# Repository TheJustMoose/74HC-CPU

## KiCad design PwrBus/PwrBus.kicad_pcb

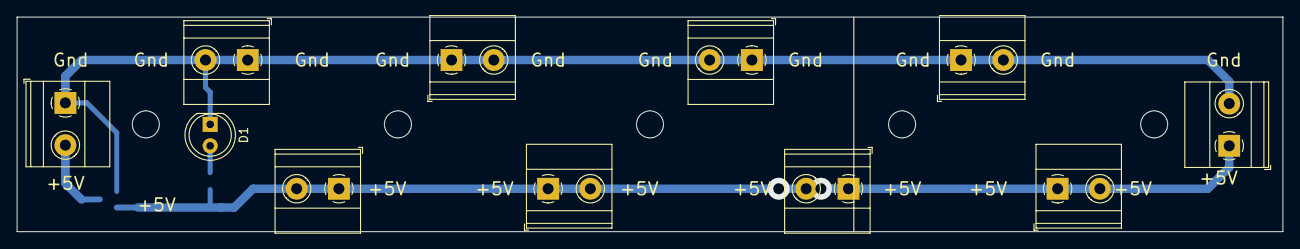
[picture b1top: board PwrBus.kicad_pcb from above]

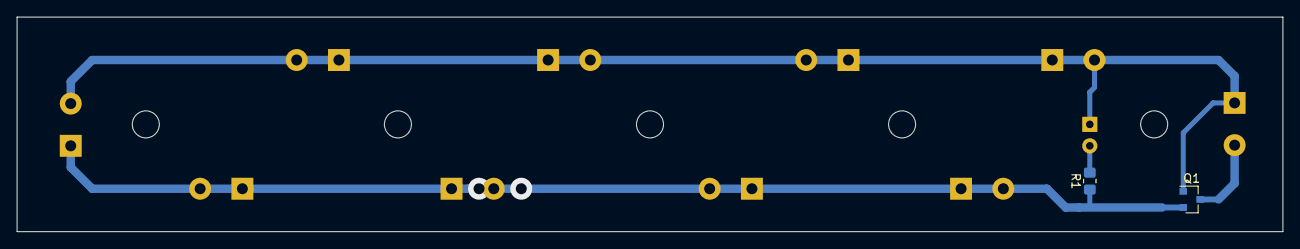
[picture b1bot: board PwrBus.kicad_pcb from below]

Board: 2 copper layers, 149.9 x 25.4 mm, 18 parts (2 on the bottom side), 4 nets.

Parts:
D1: LED; LED_D5.0mm
H1, H2, H3, H4, H5: MountingHole; MountingHole_3.2mm_M3
J1, J2, J3, J4, J5, J6, J7, J8, J9, J10: Screw_Terminal_01x02; TerminalBlock_Phoenix_MKDS-1,5-2_1x02_P5.00mm_Horizontal
Q1: IRLML5203; SOT-23
R1: 1k; R_0805_2012Metric_Pad1.20x1.40mm_HandSolder

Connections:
GND: D1.1, J1.1, J3.1, J3.2, J5.1, J5.2, J7.1, J7.2, J9.1, J9.2, J10.2, Q1.1
unnamed: D1.2, R1.2
unnamed: J1.2, Q1.3
VCC: J2.1, J2.2, J4.1, J4.2, J6.1, J6.2, J8.1, J8.2, J10.1, Q1.2, R1.1

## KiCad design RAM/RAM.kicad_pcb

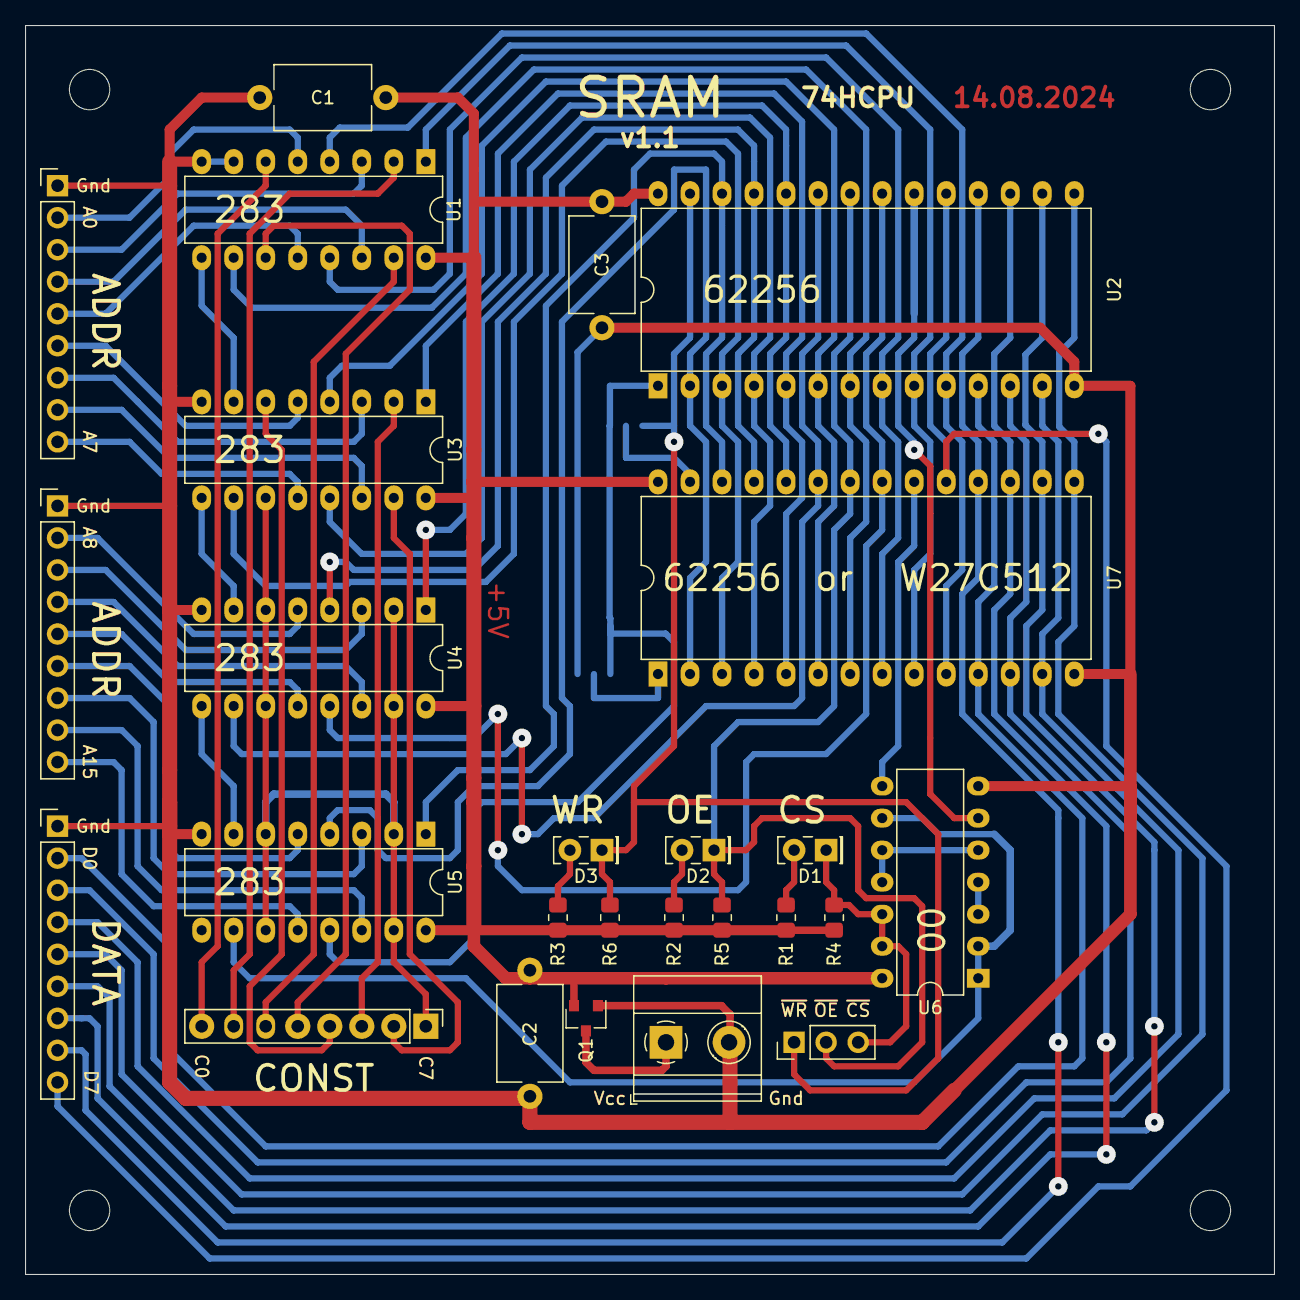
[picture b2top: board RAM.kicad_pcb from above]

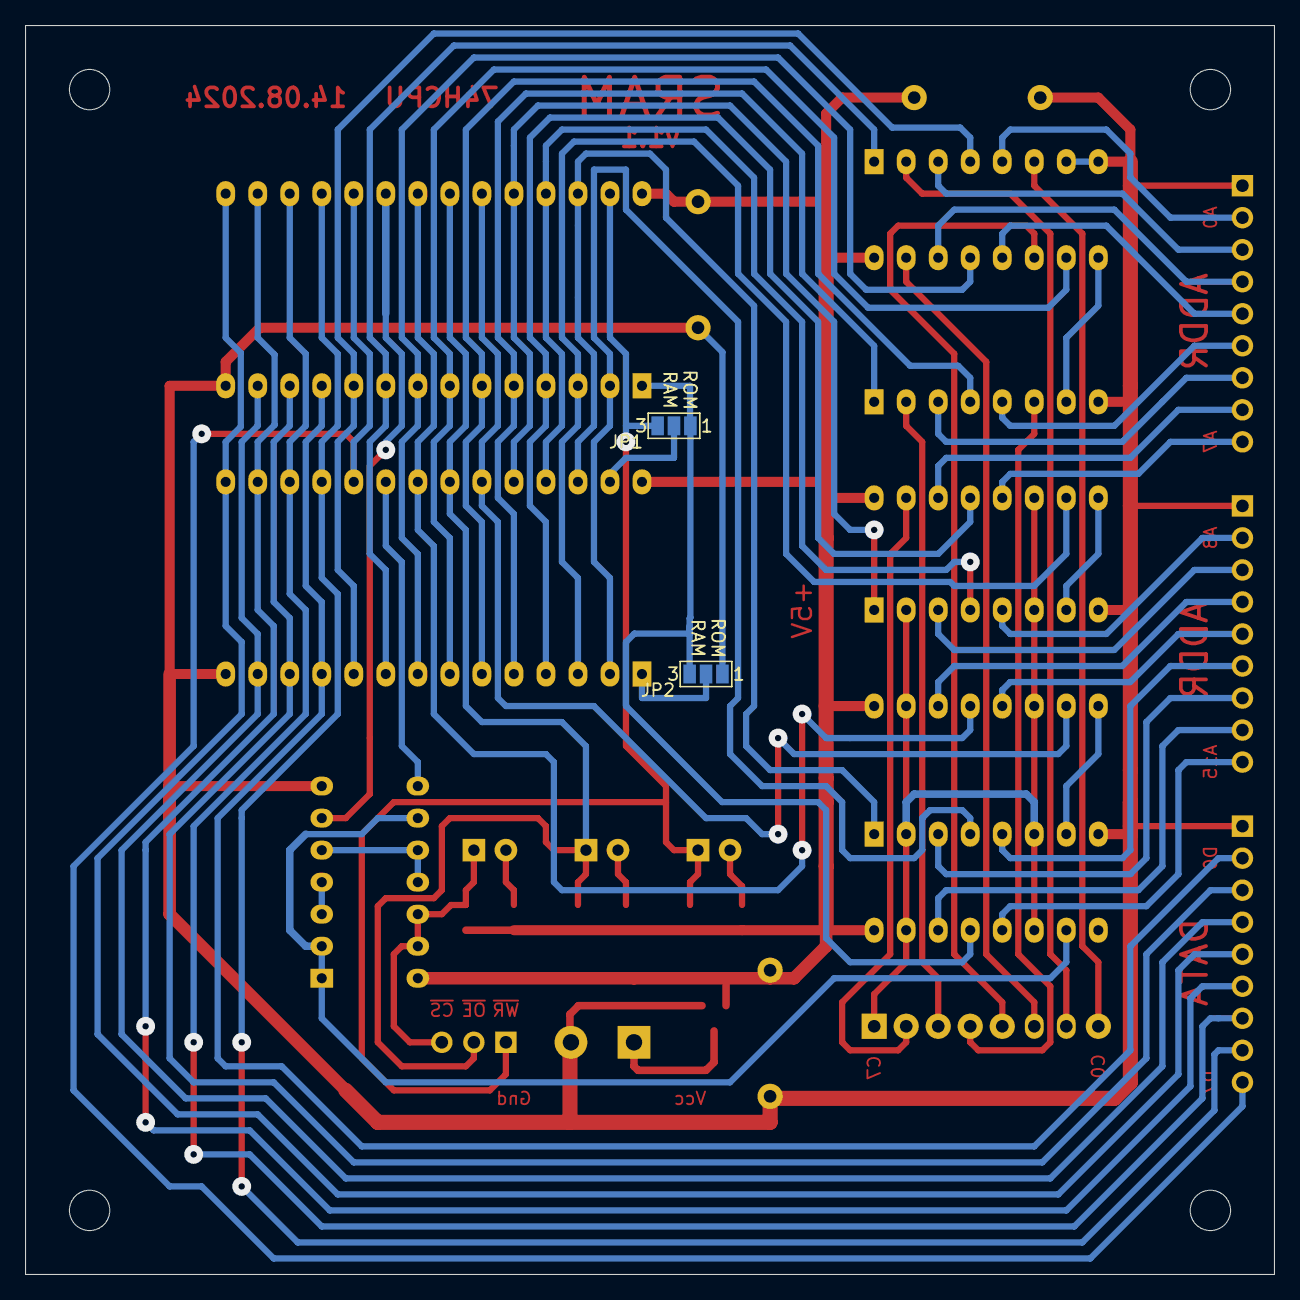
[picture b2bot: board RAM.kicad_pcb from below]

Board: 2 copper layers, 99.1 x 99.1 mm, 32 parts (2 on the bottom side), 66 nets.

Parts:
C1, C2, C3: 0.1uF; C_Disc_D7.5mm_W5.0mm_P10.00mm
D1, D2, D3: LED; LED_Rectangular_W5.0mm_H2.0mm
H1, H2, H3, H4: MountingHole; MountingHole_3.2mm_M3
J1, J2, J3: Conn_01x09_Male; PinHeader_1x09_P2.54mm_Vertical
J4: Conn_01x03_Male; PinHeader_1x03_P2.54mm_Vertical
J5: Conn_01x08_Male; PinHeader_1x08_P2.54mm_Vertical
J6: Screw_Terminal_01x02; TerminalBlock_Phoenix_MKDS-1,5-2_1x02_P5.00mm_Horizontal
JP1, JP2: SolderJumper_3_Bridged12; SolderJumper-3_P1.3mm_Open_Pad1.0x1.5mm_NumberLabels
Q1: IRLML5203; SOT-23
R1, R2, R3: 1k; R_0805_2012Metric_Pad1.20x1.40mm_HandSolder
R4, R5, R6: 10k; R_0805_2012Metric_Pad1.20x1.40mm_HandSolder
U1, U3, U4, U5: 74LS283; DIP-16_W7.62mm
U2: CY62256-70PC; DIP-28_W15.24mm
U6: 74HC00; DIP-14_W7.62mm
U7: W27C512; DIP-28_W15.24mm

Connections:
/A0: J1.2, U1.5
/A1: J1.3, U1.3
/A2: J1.4, U1.14
/A3: J1.5, U1.12
/A4: J1.6, U3.5
/A5: J1.7, U3.3
/A6: J1.8, U3.14
/A7: J1.9, U3.12
/A8: J2.2, U4.5
/A9: J2.3, U4.3
/A10: J2.4, U4.14
/A11: J2.5, U4.12
/A12: J2.6, U5.5
/A13: J2.7, U5.3
/A14: J2.8, U5.14
/A15: J2.9, U5.12
/AD0: U1.4, U2.10, U7.10
/AD1: U1.1, U2.9, U7.9
/AD2: U1.13, U2.8, U7.8
/AD3: U1.10, U2.7, U7.7
/AD4: U2.6, U3.4, U7.6
/AD5: U2.5, U3.1, U7.5
/AD6: U2.4, U3.13, U7.4
/AD7: U2.3, U3.10, U7.3
/AD8: U2.25, U4.4, U7.25
/AD9: U2.24, U4.1, U7.24
/AD10: U2.21, U4.13, U7.21
/AD11: U2.23, U4.10, U7.23
/AD12: U2.2, U5.4, U7.2
/AD13: U2.26, U5.1, U7.26
/AD14: JP1.1, JP2.3, U2.1, U5.13
/C0: J5.8, U1.6
/C1: J5.7, U1.2
/C2: J5.6, U1.15
/C3: J5.5, U1.11
/C4: J5.4, U3.6
/C5: J5.3, U3.2
/C6: J5.2, U3.15
/C7: J5.1, U3.11, U4.2, U4.6, U4.11, U4.15, U5.2, U5.6, U5.11, U5.15
/D0: J3.2, U2.11, U7.11
/D1: J3.3, U2.12, U7.12
/D2: J3.4, U2.13, U7.13
/D3: J3.5, U2.15, U7.15
/D4: J3.6, U2.16, U7.16
/D5: J3.7, U2.17, U7.17
/D6: J3.8, U2.18, U7.18
/D7: J3.9, U2.19, U7.19
/~CS: D1.1, J4.3, R4.2, U6.12, U6.13
/~CS1: U2.20, U6.6
/~CS2: U6.8, U7.20
/~OE: D2.1, J4.2, R5.2, U2.22, U7.22
/~WR: D3.1, J4.1, JP1.3, R6.2, U2.27
GND: C1.2, C2.2, C3.2, J1.1, J2.1, J3.1, J6.2, JP2.1, Q1.1, U1.7, U1.8, U2.14, U3.8, U4.8, U5.8, U6.7, U7.14
unnamed: D1.2, R1.2
unnamed: D2.2, R2.2
unnamed: D3.2, R3.2
unnamed: J6.1, Q1.3
unnamed: JP1.2, U7.27
unnamed: JP2.2, U7.1
unnamed: U1.9, U3.7
unnamed: U3.9, U4.7
unnamed: U4.9, U5.7
unnamed: U5.10, U6.1, U6.2, U6.9
unnamed: U6.3, U6.4
unnamed: U6.5, U6.10, U6.11
VCC: C1.1, C2.1, C3.1, Q1.2, R1.1, R2.1, R3.1, R4.1, R5.1, R6.1, U1.16, U2.28, U3.16, U4.16, U5.16, U6.14, U7.28

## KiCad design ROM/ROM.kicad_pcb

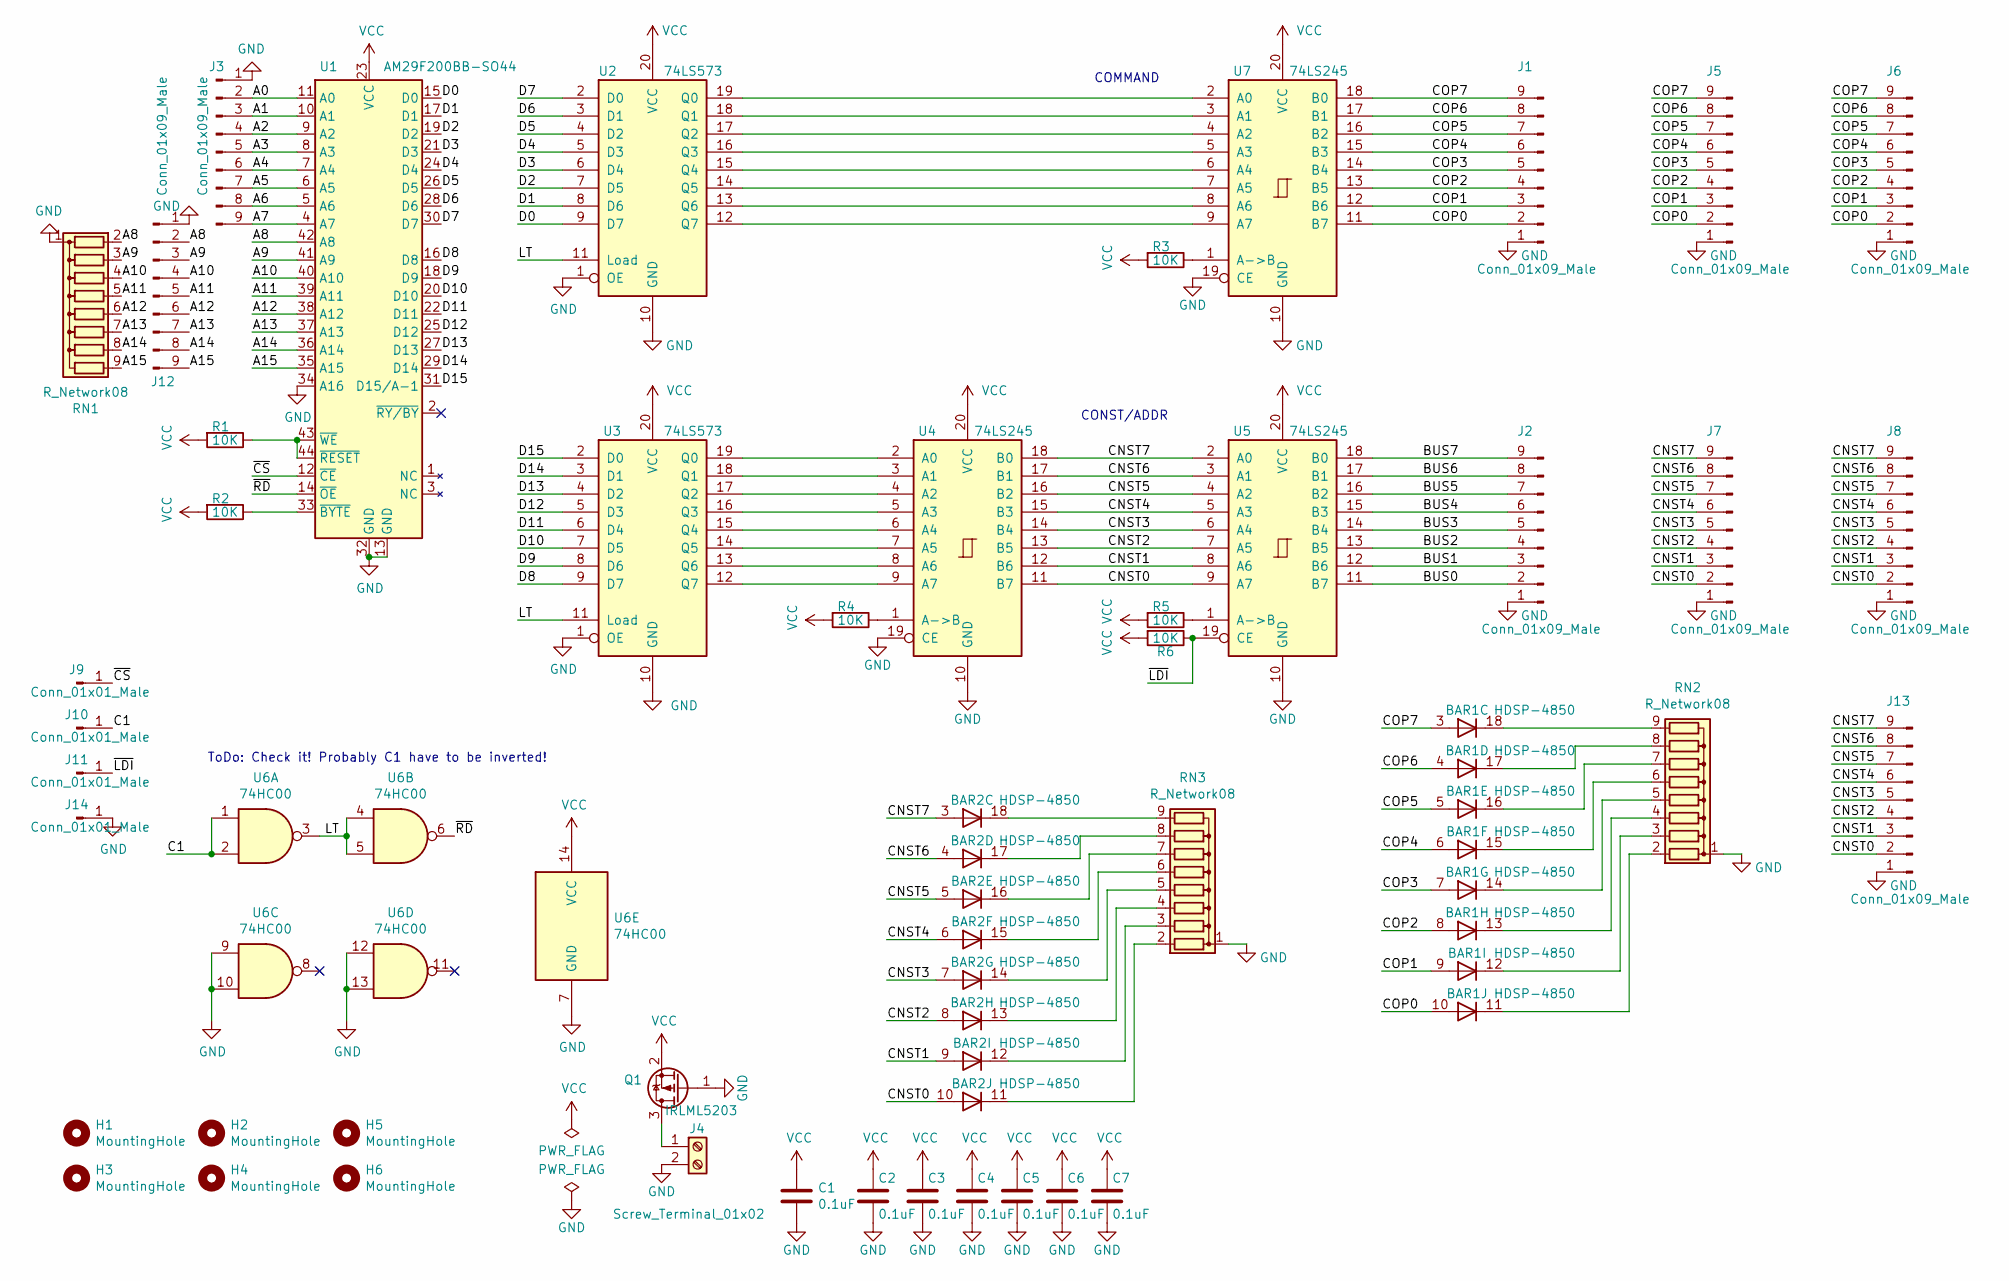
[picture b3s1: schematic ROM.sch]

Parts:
BAR1, BAR2: HDSP-4850
C1: 0.1uF; C_Rect_L24.0mm_W7.0mm_P22.50mm_MKT
C2, C3, C4, C5, C6, C7: 0.1uF; C_0805_2012Metric_Pad1.18x1.45mm_HandSolder
H1, H2, H3, H4, H5, H6: MountingHole; MountingHole_3.2mm_M3
J1, J2, J3, J5, J6, J7, J8, J12, J13: Conn_01x09_Male; PinHeader_1x09_P2.54mm_Vertical
J4: Screw_Terminal_01x02; TerminalBlock_Phoenix_PT-1,5-2-5.0-H_1x02_P5.00mm_Horizontal
J9, J10, J11, J14: Conn_01x01_Male; PinHeader_1x01_P2.54mm_Vertical
Q1: IRLML5203; SOT-23
R1, R2, R3, R4, R5, R6: 10K; R_0805_2012Metric_Pad1.20x1.40mm_HandSolder
RN1, RN2, RN3: R_Network08; R_Array_SIP9
U1: AM29F200BB-SO44; DIP-44_W15.24mm
U2, U3: 74LS573; DIP-20_W7.62mm
U4, U5, U7: 74LS245; DIP-20_W7.62mm
U6: 74HC00; DIP-14_W7.62mm

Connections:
/A0: J3.2, U1.11 (A0)
/A1: J3.3, U1.10 (A1)
/A2: J3.4, U1.9 (A2)
/A3: J3.5, U1.8 (A3)
/A4: J3.6, U1.7 (A4)
/A5: J3.7, U1.6 (A5)
/A6: J3.8, U1.5 (A6)
/A7: J3.9, U1.4 (A7)
/A8: J12.2, RN1.2 (R1), U1.42 (A8)
/A9: J12.3, RN1.3 (R2), U1.41 (A9)
/A10: J12.4, RN1.4 (R3), U1.40 (A10)
/A11: J12.5, RN1.5 (R4), U1.39 (A11)
/A12: J12.6, RN1.6 (R5), U1.38 (A12)
/A13: J12.7, RN1.7 (R6), U1.37 (A13)
/A14: J12.8, RN1.8 (R7), U1.36 (A14)
/A15: J12.9, RN1.9 (R8), U1.35 (A15)
/BUS0: J2.2, U5.11 (B7)
/BUS1: J2.3, U5.12 (B6)
/BUS2: J2.4, U5.13 (B5)
/BUS3: J2.5, U5.14 (B4)
/BUS4: J2.6, U5.15 (B3)
/BUS5: J2.7, U5.16 (B2)
/BUS6: J2.8, U5.17 (B1)
/BUS7: J2.9, U5.18 (B0)
/C1: J10.1, U6.1, U6.2
/CNST0: BAR2.10 (A), J7.2, J8.2, J13.2, U4.11 (B7), U5.9 (A7)
/CNST1: BAR2.9 (A), J7.3, J8.3, J13.3, U4.12 (B6), U5.8 (A6)
/CNST2: BAR2.8 (A), J7.4, J8.4, J13.4, U4.13 (B5), U5.7 (A5)
/CNST3: BAR2.7 (A), J7.5, J8.5, J13.5, U4.14 (B4), U5.6 (A4)
/CNST4: BAR2.6 (A), J7.6, J8.6, J13.6, U4.15 (B3), U5.5 (A3)
/CNST5: BAR2.5 (A), J7.7, J8.7, J13.7, U4.16 (B2), U5.4 (A2)
/CNST6: BAR2.4 (A), J7.8, J8.8, J13.8, U4.17 (B1), U5.3 (A1)
/CNST7: BAR2.3 (A), J7.9, J8.9, J13.9, U4.18 (B0), U5.2 (A0)
/COP0: BAR1.10 (A), J1.2, J5.2, J6.2, U7.11 (B7)
/COP1: BAR1.9 (A), J1.3, J5.3, J6.3, U7.12 (B6)
/COP2: BAR1.8 (A), J1.4, J5.4, J6.4, U7.13 (B5)
/COP3: BAR1.7 (A), J1.5, J5.5, J6.5, U7.14 (B4)
/COP4: BAR1.6 (A), J1.6, J5.6, J6.6, U7.15 (B3)
/COP5: BAR1.5 (A), J1.7, J5.7, J6.7, U7.16 (B2)
/COP6: BAR1.4 (A), J1.8, J5.8, J6.8, U7.17 (B1)
/COP7: BAR1.3 (A), J1.9, J5.9, J6.9, U7.18 (B0)
/D0: U1.15 (D0), U2.9 (D7)
/D1: U1.17 (D1), U2.8 (D6)
/D2: U1.19 (D2), U2.7 (D5)
/D3: U1.21 (D3), U2.6 (D4)
/D4: U1.24 (D4), U2.5 (D3)
/D5: U1.26 (D5), U2.4 (D2)
/D6: U1.28 (D6), U2.3 (D1)
/D7: U1.30 (D7), U2.2 (D0)
/D8: U1.16 (D8), U3.9 (D7)
/D9: U1.18 (D9), U3.8 (D6)
/D10: U1.20 (D10), U3.7 (D5)
/D11: U1.22 (D11), U3.6 (D4)
/D12: U1.25 (D12), U3.5 (D3)
/D13: U1.27 (D13), U3.4 (D2)
/D14: U1.29 (D14), U3.3 (D1)
/D15: U1.31 (D15/A-1), U3.2 (D0)
/LT: U2.11 (Load), U3.11 (Load), U6.3, U6.4, U6.5
/~CS: J9.1, U1.12 (~CE)
/~LDI: J11.1, R6.1, U5.19 (CE)
/~RD: U1.14 (~OE), U6.6
GND: C1.2, C2.2, C3.2, C4.2, C5.2, C6.2, C7.2, J1.1, J2.1, J3.1, J4.2, J5.1, J6.1, J7.1, J8.1, J12.1, J13.1, J14.1, Q1.1 (G), RN1.1 (common), RN2.1 (common), RN3.1 (common), U1.13 (GND), U1.32 (GND), U1.34 (A16), U2.1 (OE), U2.10 (GND), U3.1 (OE), U3.10 (GND), U4.10 (GND), U4.19 (CE), U5.10 (GND), U6.7 (GND), U6.9, U6.10, U6.12, U6.13, U7.10 (GND), U7.19 (CE)
unnamed: BAR1.11 (K), RN2.2 (R1)
unnamed: BAR1.12 (K), RN2.3 (R2)
unnamed: BAR1.13 (K), RN2.4 (R3)
unnamed: BAR1.14 (K), RN2.5 (R4)
unnamed: BAR1.15 (K), RN2.6 (R5)
unnamed: BAR1.16 (K), RN2.7 (R6)
unnamed: BAR1.17 (K), RN2.8 (R7)
unnamed: BAR1.18 (K), RN2.9 (R8)
unnamed: BAR2.11 (K), RN3.2 (R1)
unnamed: BAR2.12 (K), RN3.3 (R2)
unnamed: BAR2.13 (K), RN3.4 (R3)
unnamed: BAR2.14 (K), RN3.5 (R4)
unnamed: BAR2.15 (K), RN3.6 (R5)
unnamed: BAR2.16 (K), RN3.7 (R6)
unnamed: BAR2.17 (K), RN3.8 (R7)
unnamed: BAR2.18 (K), RN3.9 (R8)
unnamed: J4.1, Q1.3 (D)
unnamed: R1.1, U1.43 (~WE), U1.44 (~RESET)
unnamed: R2.1, U1.33 (~BYTE)
unnamed: R3.1, U7.1 (A->B)
unnamed: R4.1, U4.1 (A->B)
unnamed: R5.1, U5.1 (A->B)
unnamed: U2.12 (Q7), U7.9 (A7)
unnamed: U2.13 (Q6), U7.8 (A6)
unnamed: U2.14 (Q5), U7.7 (A5)
unnamed: U2.15 (Q4), U7.6 (A4)
unnamed: U2.16 (Q3), U7.5 (A3)
unnamed: U2.17 (Q2), U7.4 (A2)
unnamed: U2.18 (Q1), U7.3 (A1)
unnamed: U2.19 (Q0), U7.2 (A0)
unnamed: U3.12 (Q7), U4.9 (A7)
unnamed: U3.13 (Q6), U4.8 (A6)
unnamed: U3.14 (Q5), U4.7 (A5)
unnamed: U3.15 (Q4), U4.6 (A4)
unnamed: U3.16 (Q3), U4.5 (A3)
unnamed: U3.17 (Q2), U4.4 (A2)
unnamed: U3.18 (Q1), U4.3 (A1)
unnamed: U3.19 (Q0), U4.2 (A0)
VCC: C1.1, C2.1, C3.1, C4.1, C5.1, C6.1, C7.1, Q1.2 (S), R1.2, R2.2, R3.2, R4.2, R5.2, R6.2, U1.23 (VCC), U2.20 (VCC), U3.20 (VCC), U4.20 (VCC), U5.20 (VCC), U6.14 (VCC), U7.20 (VCC)

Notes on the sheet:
COMMAND
CONST/ADDR
ToDo: Check it! Probably C1 have to be inverted!

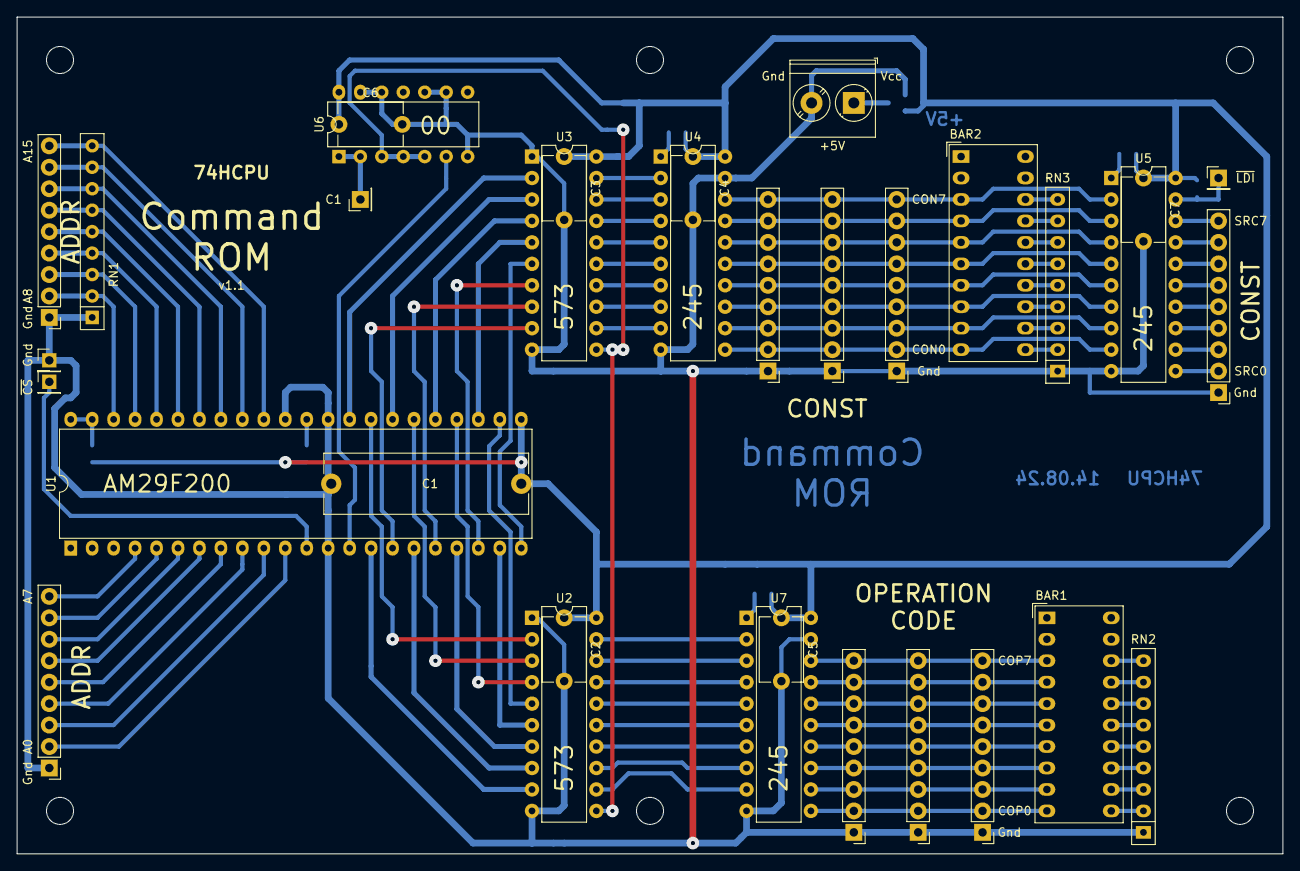
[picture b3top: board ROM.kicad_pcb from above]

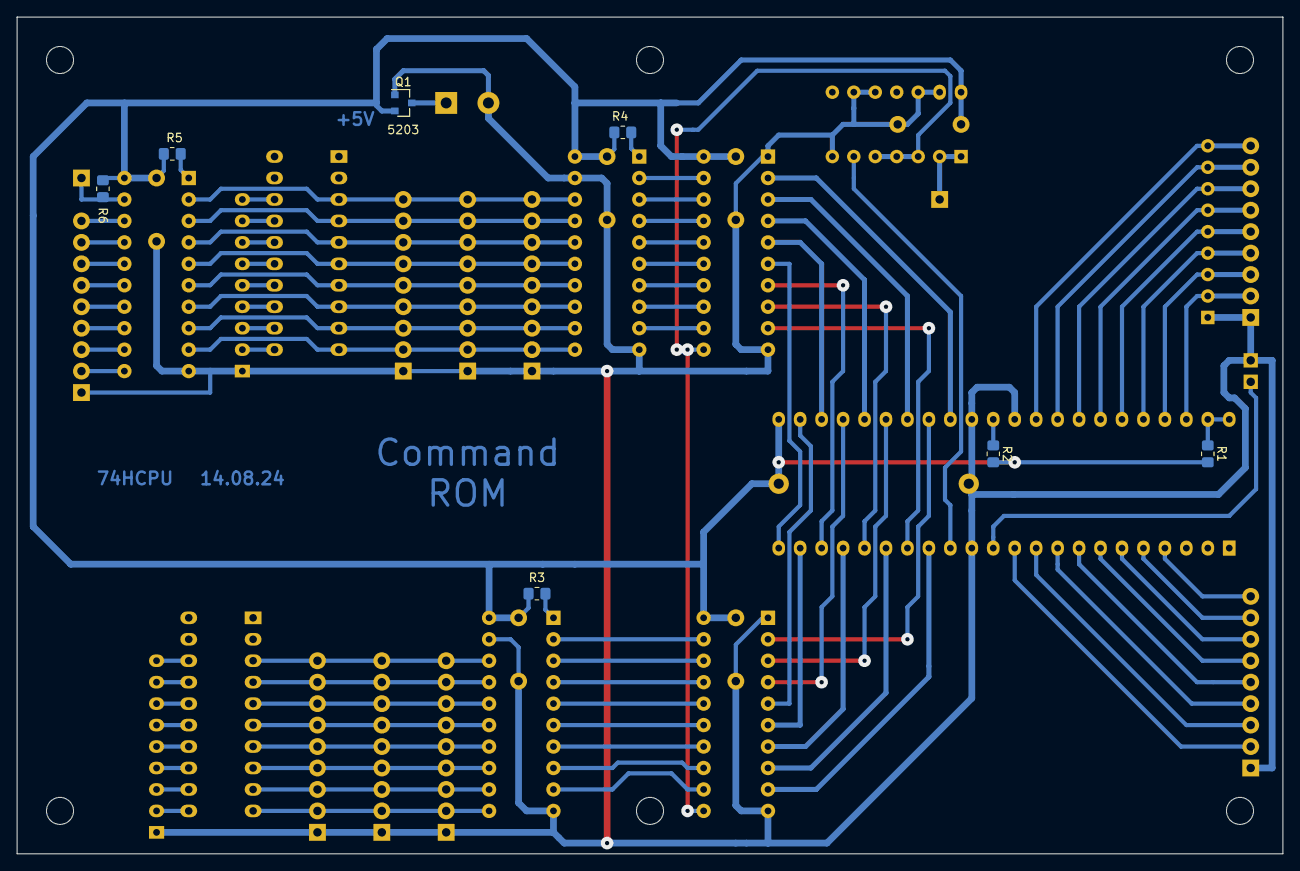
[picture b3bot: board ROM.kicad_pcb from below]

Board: 2 copper layers, 149.9 x 99.1 mm, 46 parts (7 on the bottom side), 101 nets.

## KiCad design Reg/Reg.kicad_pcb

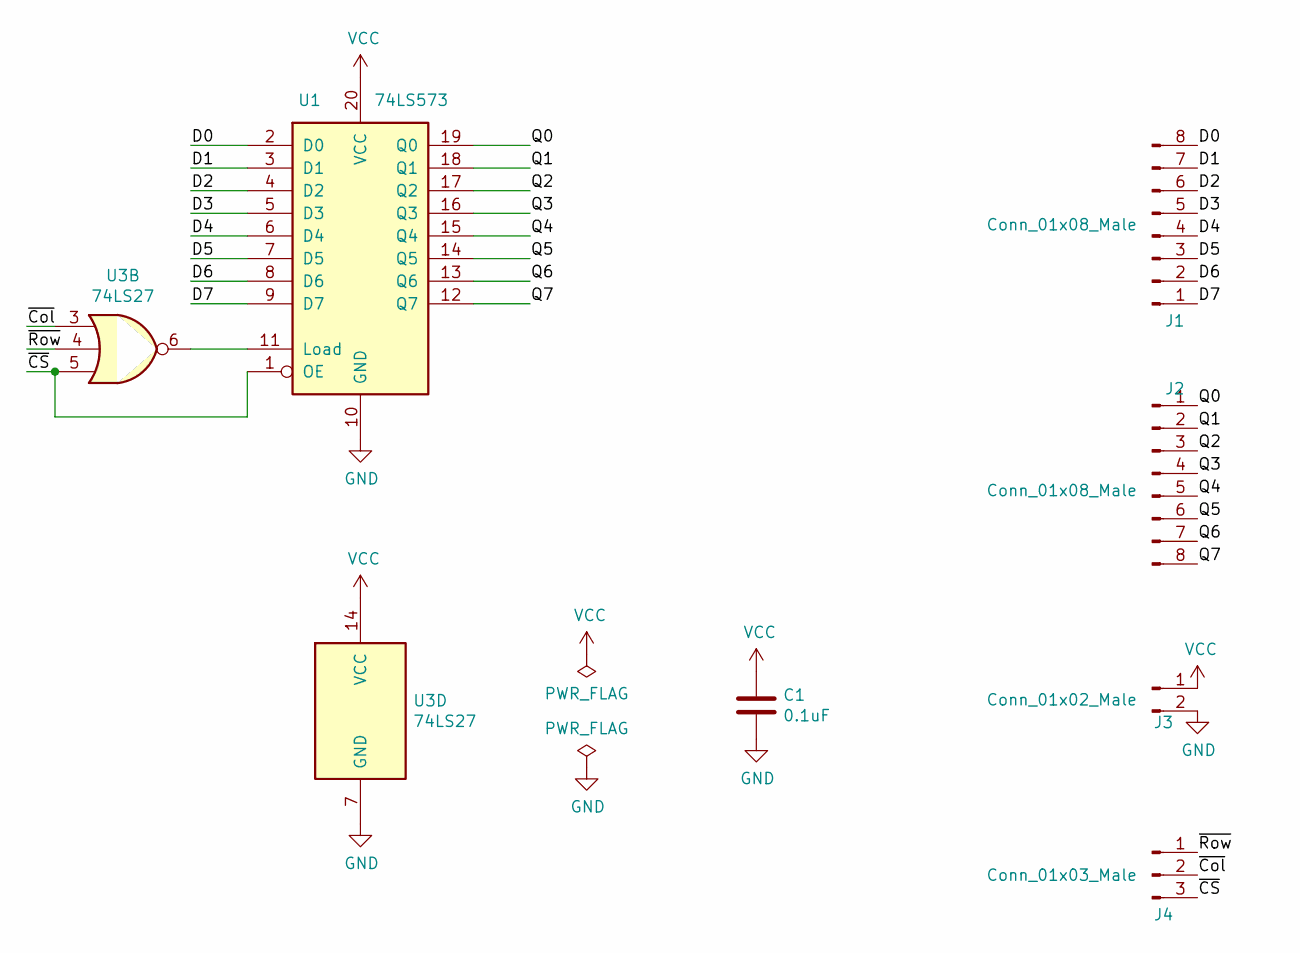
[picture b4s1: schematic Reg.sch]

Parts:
C1: 0.1uF; C_0805_2012Metric_Pad1.18x1.45mm_HandSolder
J1, J2: Conn_01x08_Male; PinHeader_1x08_P2.54mm_Horizontal
J3: Conn_01x02_Male; PinHeader_1x02_P2.54mm_Horizontal
J4: Conn_01x03_Male; PinHeader_1x03_P2.54mm_Horizontal
U1: 74LS573; SOP-20_7.5x12.8mm_P1.27mm
U3: 74LS27; SO-14_3.9x8.65mm_P1.27mm

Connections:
/D0: J1.8, U1.2 (D0)
/D1: J1.7, U1.3 (D1)
/D2: J1.6, U1.4 (D2)
/D3: J1.5, U1.5 (D3)
/D4: J1.4, U1.6 (D4)
/D5: J1.3, U1.7 (D5)
/D6: J1.2, U1.8 (D6)
/D7: J1.1, U1.9 (D7)
/Q0: J2.1, U1.19 (Q0)
/Q1: J2.2, U1.18 (Q1)
/Q2: J2.3, U1.17 (Q2)
/Q3: J2.4, U1.16 (Q3)
/Q4: J2.5, U1.15 (Q4)
/Q5: J2.6, U1.14 (Q5)
/Q6: J2.7, U1.13 (Q6)
/Q7: J2.8, U1.12 (Q7)
/~CS: J4.3, U1.1 (OE), U3.5
/~Col: J4.2, U3.3
/~Row: J4.1, U3.4
GND: C1.2, J3.2, U1.10 (GND), U3.7 (GND)
unnamed: U1.11 (Load), U3.6
VCC: C1.1, J3.1, U1.20 (VCC), U3.14 (VCC)

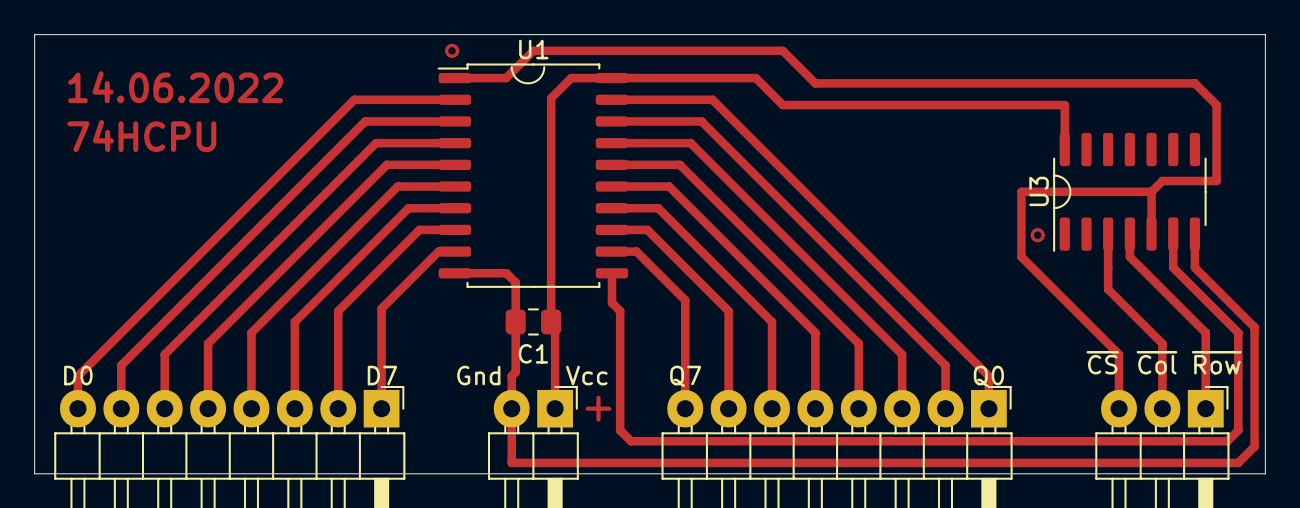
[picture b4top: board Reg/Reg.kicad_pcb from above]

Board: 2 copper layers, 72.1 x 25.7 mm, 7 parts (0 on the bottom side), 22 nets.

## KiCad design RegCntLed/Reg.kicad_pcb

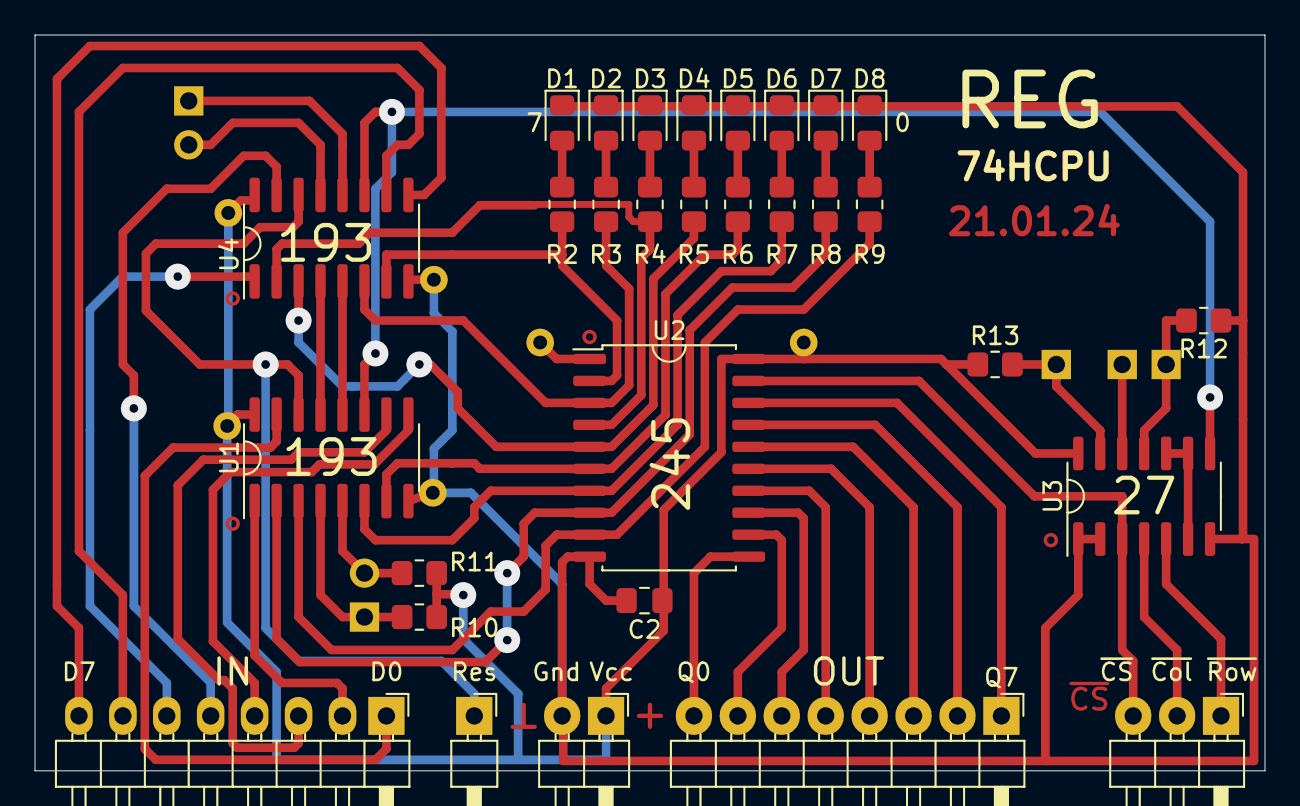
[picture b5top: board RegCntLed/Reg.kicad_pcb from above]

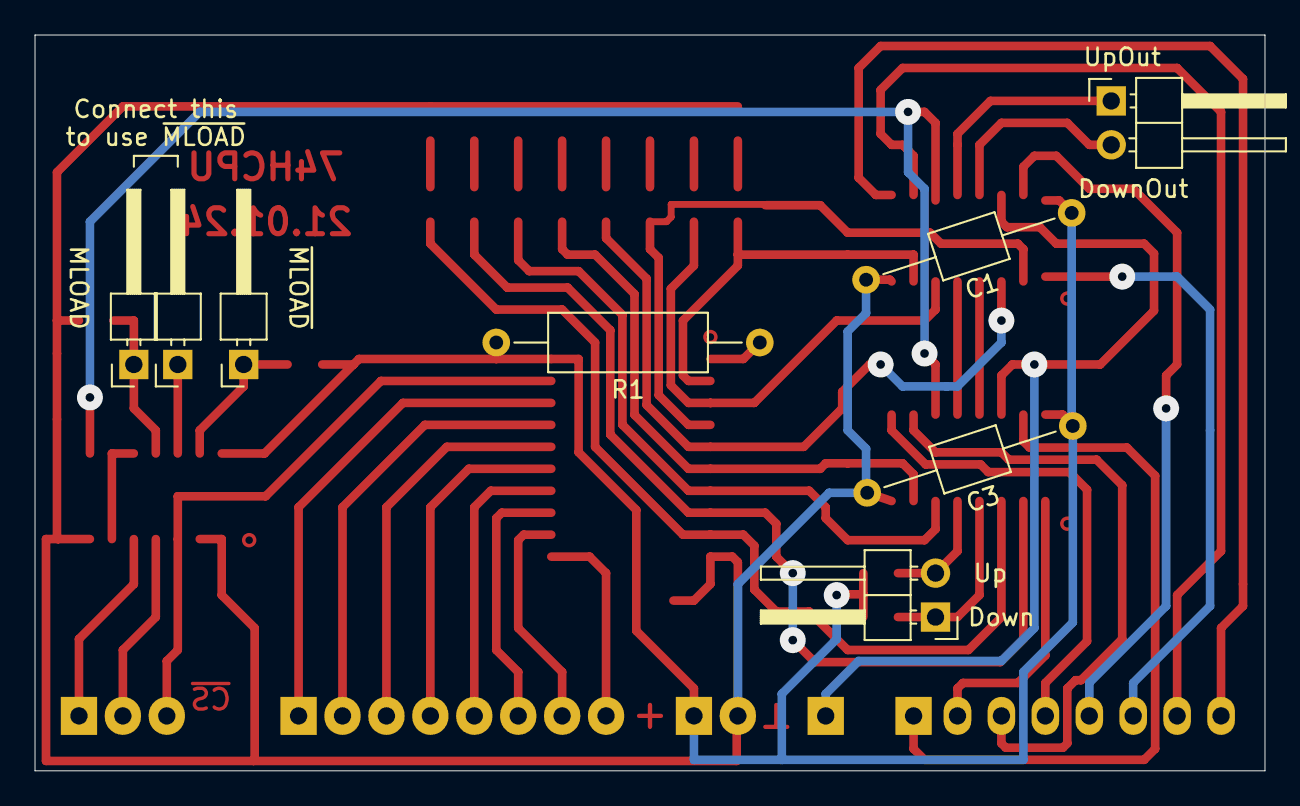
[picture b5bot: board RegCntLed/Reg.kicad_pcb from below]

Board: 2 copper layers, 71.1 x 42.5 mm, 38 parts (8 on the bottom side), 50 nets.

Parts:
C1, C3: 0.1uF; C_Axial_L3.8mm_D2.6mm_P12.50mm_Horizontal
C2: 0.1uF; C_0805_2012Metric_Pad1.18x1.45mm_HandSolder
D1, D2, D3, D4, D5, D6, D7, D8: LED; LED_0805_2012Metric_Pad1.15x1.40mm_HandSolder
J1, J2: Conn_01x08_Male; PinHeader_1x08_P2.54mm_Horizontal
J3, J5, J6: Conn_01x02_Male; PinHeader_1x02_P2.54mm_Horizontal
J4: Conn_01x03_Male; PinHeader_1x03_P2.54mm_Horizontal
J7, J8, J9, J10: Conn_01x01_Male; PinHeader_1x01_P2.54mm_Horizontal
R1: 10k; R_Axial_DIN0309_L9.0mm_D3.2mm_P15.24mm_Horizontal
R2, R3, R4, R5, R6, R7, R8, R9: 1k; R_0805_2012Metric_Pad1.20x1.40mm_HandSolder
R10, R11, R12, R13: 10k; R_0805_2012Metric_Pad1.20x1.40mm_HandSolder
U1, U4: 74LS193; SOP-16_3.9x9.9mm_P1.27mm
U2: 74HC245; SOP-20_7.5x12.8mm_P1.27mm
U3: 74LS27; SO-14_3.9x8.65mm_P1.27mm

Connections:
/D0: J1.1, U1.15
/D1: J1.2, U1.1
/D2: J1.3, U1.10
/D3: J1.4, U1.9
/D4: J1.5, U4.15
/D5: J1.6, U4.1
/D6: J1.7, U4.10
/D7: J1.8, U4.9
/Down: J6.1, R10.1, U1.4
/DownLH: U1.13, U4.4
/DownOut: J5.2, U4.13
/L0: R9.1, U1.3, U2.9
/L1: R8.1, U1.2, U2.8
/L2: R7.1, U1.6, U2.7
/L3: R6.1, U1.7, U2.6
/L4: R5.1, U2.5, U4.3
/L5: R4.1, U2.4, U4.2
/L6: R3.1, U2.3, U4.6
/L7: R2.1, U2.2, U4.7
/MLOAD: J8.1, R12.2, U3.11
/Q0: J2.8, U2.11
/Q1: J2.7, U2.12
/Q2: J2.6, U2.13
/Q3: J2.5, U2.14
/Q4: J2.4, U2.15
/Q5: J2.3, U2.16
/Q6: J2.2, U2.17
/Q7: J2.1, U2.18
/Res: J7.1, U1.14, U4.14
/Up: J6.2, R11.1, U1.5
/UpLH: U1.12, U4.5
/UpOut: J5.1, U4.12
/~CS: J4.3, U2.19, U3.3
/~Col: J4.2, U3.4
/~LOAD: U1.11, U3.8, U4.11
/~MLOAD: J9.1, R13.2, U3.13
/~Row: J4.1, U3.5
GND: C1.2, C2.2, C3.2, D1.1, D2.1, D3.1, D4.1, D5.1, D6.1, D7.1, D8.1, J3.2, R12.1, U1.8, U2.10, U3.1, U3.2, U3.7, U4.8
unnamed: D1.2, R2.2
unnamed: D2.2, R3.2
unnamed: D3.2, R4.2
unnamed: D4.2, R5.2
unnamed: D5.2, R6.2
unnamed: D6.2, R7.2
unnamed: D7.2, R8.2
unnamed: D8.2, R9.2
unnamed: J10.1, U3.12
unnamed: R1.1, U2.1
unnamed: U3.6, U3.9, U3.10
VCC: C1.1, C2.1, C3.1, J3.1, R1.2, R10.2, R11.2, R13.1, U1.16, U2.20, U3.14, U4.16
